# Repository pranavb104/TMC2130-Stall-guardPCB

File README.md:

# TMC2130-Stall-guardPCB

A breakout PCB equipped with an atmega328p(Arduino) and TMC2130 driver board.

This PCB was originally designed to control the flow of a syringe pump. The TMC2130 provides an SPI interface to detect spikes in current (StallGuard feature) which can be used to replace a limit switch. The stallguard value needs to be calibrated according to the motor you use.

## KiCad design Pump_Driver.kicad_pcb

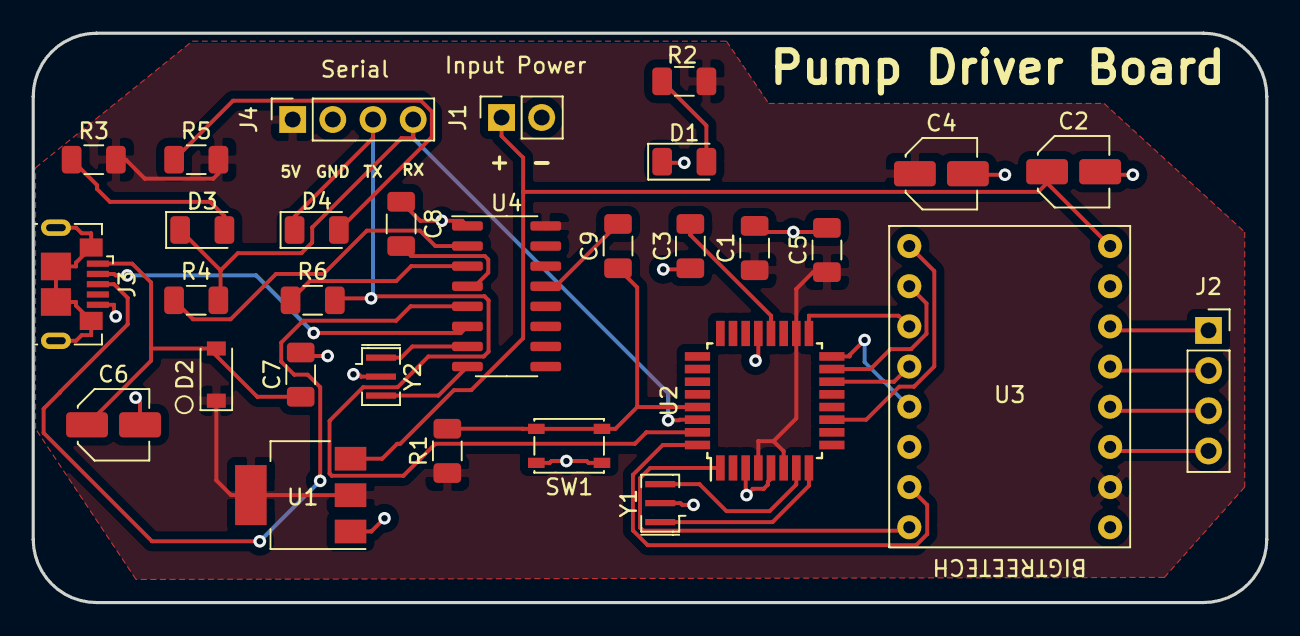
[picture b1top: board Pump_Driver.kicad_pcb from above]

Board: 2 copper layers, 78.0 x 36.0 mm, 30 parts (0 on the bottom side), 32 nets.

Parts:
C1, C5: 1uF; C_1206_3216Metric
C2: 10uF; C_Elec_4x5.4
C3, C7, C8, C9: 100nF; C_1206_3216Metric
C4, C6: 4.7uF_16v; C_Elec_4x5.4
D1: Yellow LED; LED_1206_3216Metric
D2: BAT42W-V; D_SOD-123
D3: Green LED; LED_1206_3216Metric
D4: Red LED; LED_1206_3216Metric
J1: Input Voltage; PinSocket_1x02_P2.54mm_Vertical
J2: Motor Leads; PinSocket_1x04_P2.54mm_Vertical
J3: USB_B_Micro; USB_Micro-B_GCT_USB3076-30-A
J4: Serial; PinSocket_1x04_P2.54mm_Vertical
R1, R2, R3, R4, R5, R6: 1K; R_1206_3216Metric
SW1: SW1_Reset; SW_SPST_PTS810
U1: AMS1117-5.0; SOT-223-3_TabPin2
U2: ATmega328P-AU; TQFP-32_7x7mm_P0.8mm
U3: TMC2130_BS; tmc_2208
U4: CH340G; SOIC-16_3.9x9.9mm_P1.27mm
Y1: 16MhZ Crystal; Resonator_SMD_muRata_CSTxExxV-3Pin_3.0x1.1mm
Y2: 12MhZ Crystal; Resonator_SMD_muRata_CSTxExxV-3Pin_3.0x1.1mm

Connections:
+3V3: C8.2, U4.4
+5V: C1.1, C4.1, C5.1, D2.1, J4.1, R1.1, R2.2, R3.2, R5.2, U1.2, U2.4, U2.6, U2.18, U3.10, U4.16
D2: U2.32, U3.7
D3: U2.1, U3.8
D7: U2.11, U3.1
D10: U2.14, U3.4
GND: C1.2, C2.2, C3.2, C4.2, C5.2, C6.2, C7.2, C8.1, D1.1, J1.2, J3.5, J4.2, SW1.1, U1.1, U2.3, U2.5, U2.21, U3.15, U4.1, Y1.2, Y2.2
MISO: U2.16, U3.5
MOSI: U2.15, U3.2
unnamed: C3.1, U2.20
unnamed: C9.2, U4.13
unnamed: D1.2, R2.1
unnamed: D3.2, R3.1
unnamed: D4.2, R5.1
unnamed: J2.1, U3.14
unnamed: J2.2, U3.13
unnamed: J2.3, U3.12
unnamed: J2.4, U3.11
unnamed: J3.2, U4.6
unnamed: J3.3, U4.5
unnamed: R4.1, U4.2
unnamed: R6.1, U4.3
unnamed: U2.7, Y1.3
unnamed: U2.8, Y1.1
unnamed: U4.7, Y2.1
unnamed: U4.8, Y2.3
RESET: C9.1, R1.2, SW1.2, U2.29
RX: D3.1, J4.4, R4.2, U2.30
SCK: U2.17, U3.3
TX: D4.1, J4.3, R6.2, U2.31
VIN: C2.1, J1.1, U1.3, U3.16
VUSB: C6.1, C7.1, D2.2, J3.1
